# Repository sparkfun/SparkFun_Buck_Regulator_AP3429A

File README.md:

SparkFun AP3429A Buck Regulator Breakouts
========================================

<p align="center">

</p>

| [3.3V Buck Regulator (COM-21337)](https://www.sparkfun.com/products/21337) | [1.8V Buck Regulator (COM-21338)](https://www.sparkfun.com/products/21338) |
| --- | --- |
|  |  |

These buck regulator boards feature the AP3429A from [Diodes Inc.](https://www.diodes.com/), a 2A DC-DC buck converter with a wide input voltage range of 2.7V to 5.5V. The boards are configured to provide a regulated **3.3V** or **1.8V** output, which is controlled by an `EN` *(enable)* pin and indicated by a red power LED. A pre-assembled screw terminal and 0.1" spaced PTH pins are available to connect the input and output power of the boards. Additionally, there is the option to solder on a [barrel jack](https://www.sparkfun.com/products/119) for an [external power supply](https://www.sparkfun.com/categories/308). To dissipate excess heat, a copper pad is provided to attach a heat sink to the bottom of the board.

*The primary differences between these boards are their regulated output voltage (**1.8V** and **3.3V**) and the configured UVLO (**2.7V** and **3.9V**, respectively).*

Repository Contents
-------------------

* **[/docs](/docs/)** - Online documentation files
    * [board_files](/docs/board_files/) - Files for the product design
        * [Eagle design files](/docs/board_files/eagle_files.zip) (.zip)
        * [Schematic](/docs/board_files/schematic.pdf) (.pdf)
        * [Dimensions](/docs/board_files/dimensions.pdf) (.pdf)
    * [component_documentation](/docs/component_documentation/) - Datasheets for hardware components
    * [img/hookup_guide/](/docs/img/hookup_guide/) - Images for hookup guide documentation
* **[/Hardware](/Hardware/)** - Eagle design files (.brd, .sch)

Documentation
--------------
* **[Hookup Guide (mkdocs)](http://docs.sparkfun.com/SparkFun_Buck_Regulator_AP3429A/)** - Hookup Guide for the AP3429A Buck Regulator Breakouts

Product Variants
----------------
* **AP63357** - 5V Buck Regulators
    * COM-21255: [SparkFun Buck Regulator Breakout - 5V (AP63357DV)](https://www.sparkfun.com/products/21255)
    * COM-21256: [SparkFun BabyBuck Regulator Breakout - 5V (AP63357DV)](https://www.sparkfun.com/products/21256)
* **AP63203** - 3.3V Buck Regulators
    * COM-18356: [SparkFun Buck Regulator Breakout - 3.3V (AP63203)](https://www.sparkfun.com/products/18356)
    * COM-18357: [SparkFun BabyBuck Regulator Breakout - 3.3V (AP63203)](https://www.sparkfun.com/products/18357)
* **AP3429A** - 3.3V & 1.8V Buck Regulators
    * COM-21337: [SparkFun Buck Regulator Breakout - 3.3V (AP3429A)](https://www.sparkfun.com/products/21337)
    * COM-21338: [SparkFun Buck Regulator Breakout - 1.8V (AP3429A)](https://www.sparkfun.com/products/21338)

Version History
---------------
* [v01](https://github.com/sparkfun/SparkFun_Buck_Regulator_AP3429A/releases/tag/v01) - Initial Release

License Information
-------------------

This product is _**open source**_! 

Please review the LICENSE.md file for license information. 

If you have any questions or concerns about licensing, please contact technical support on our [SparkFun forums](https://forum.sparkfun.com/viewforum.php?f=152).

Distributed as-is; no warranty is given.

- Your friends at SparkFun.

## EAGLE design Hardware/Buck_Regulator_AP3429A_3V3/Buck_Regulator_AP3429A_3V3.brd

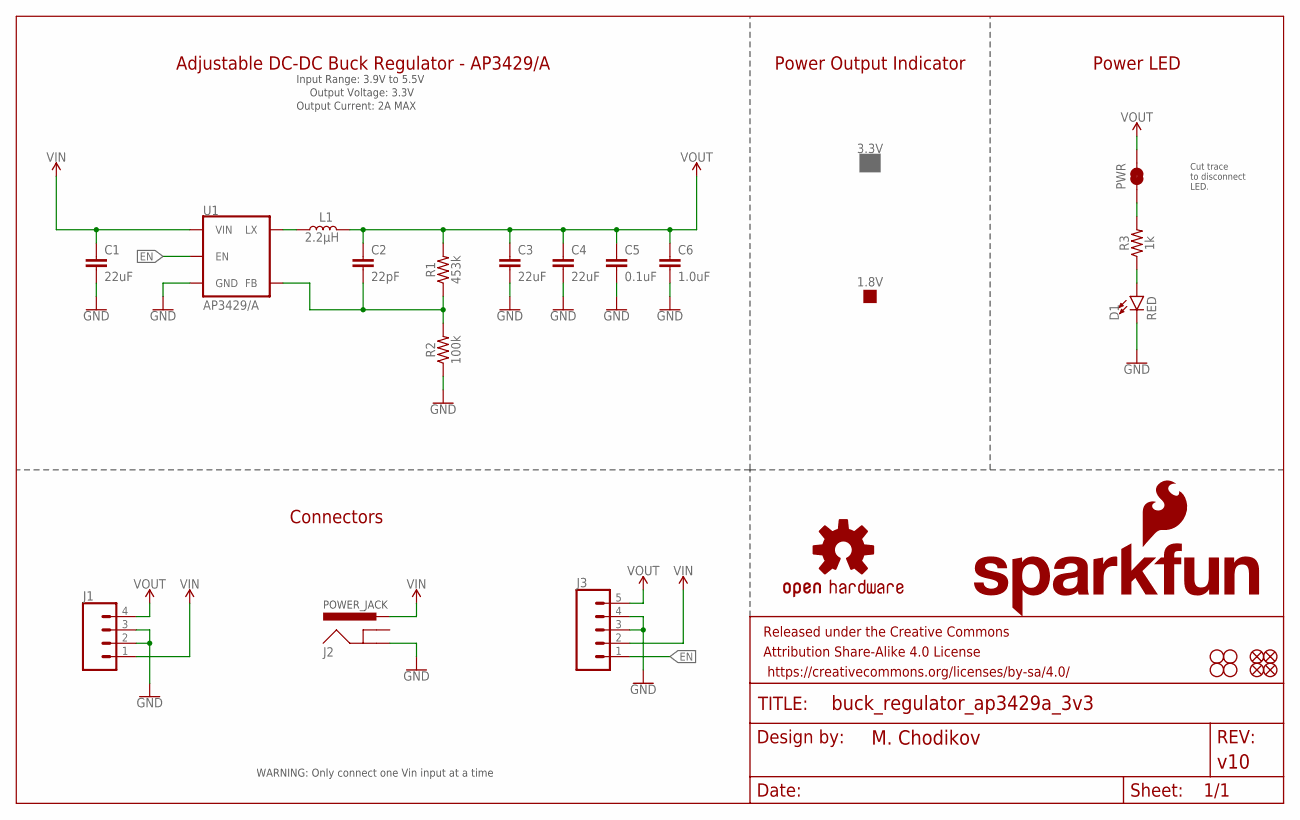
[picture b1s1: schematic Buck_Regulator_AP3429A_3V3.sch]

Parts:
1.8V: PROD_ID_NO-PASTE_NO_SILK; PRODUCT_IDENT_NO_NO-SILK
3.3V: PROD_ID_PASTE_NO-SILK; PRODUCT_IDENT_PASTE_NO-SILK
C1, C3, C4: 22uF; 0805
C2: 22pF; 0402-TIGHT
C5: 0.1uF; 0603
C6: 1.0uF; 0603
D1: RED; LED-0603
FD1, FD2, FD3, FD4: FIDUCIALUFIDUCIAL; FIDUCIAL-MICRO
FRAME1: FRAME-LEDGER; CREATIVE_COMMONS
H1, H2, H3, H4: STAND-OFFTIGHT; STAND-OFF-TIGHT
J1: Screw Terminal; SCREWTERMINAL-3.5MM-4
J2: POWER_JACKPOWER_JACK_SLOT_COMBO; POWER_JACK_PTH_SLOT_BOTH
J3: Breakout Headers; 1X05_NO_SILK
L1: 2.2μH; INDUCTOR_4X4MM
LOGO1: OSHW-LOGOS; OSHW-LOGO-S
LOGO2: SFE_LOGO_NAME.1_INCH; SFE_LOGO_NAME_.1
LOGO3: SFE_LOGO_FLAME.1_INCH; SFE_LOGO_FLAME_.1
PWR: JUMPER-SMT_2_NC_TRACE_SILK; SMT-JUMPER_2_NC_TRACE_SILK
R1: 453k; 0603
R2: 100k; 0603
R3: 1k; 0603
U1: AP3429/A; SOT23-5

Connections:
EN: J3.1, U1.1 (EN)
GND: C1.2, C3.2, C4.2, C5.2, C6.2, D1.C, J1.2, J1.3, J2.GND, J3.3, J3.4, R2.1, U1.2 (GND)
unnamed: L1.P$1 (1), U1.3 (LX)
unnamed: C2.2, R1.1, R2.2, U1.5 (FB)
unnamed: PWR.1, R3.2
unnamed: D1.A, R3.1
VIN: C1.1, J1.1, J2.PWR, J3.2, U1.4 (VIN)
VOUT: C2.1, C3.1, C4.1, C5.1, C6.1, J1.4, J3.5, L1.P$2 (2), PWR.2, R1.2

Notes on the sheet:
Input Range: 3.9V to 5.5V
Adjustable DC-DC Buck Regulator - AP3429/A
Power LED
Connectors
POWER_JACK
Output Current: 2A MAX
WARNING: Only connect one Vin input at a time
Power Output Indicator
Cut trace to disconnect LED.
Output Voltage: 3.3V

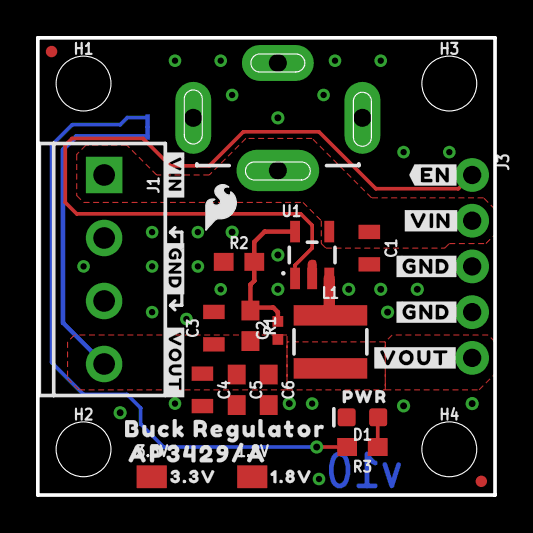
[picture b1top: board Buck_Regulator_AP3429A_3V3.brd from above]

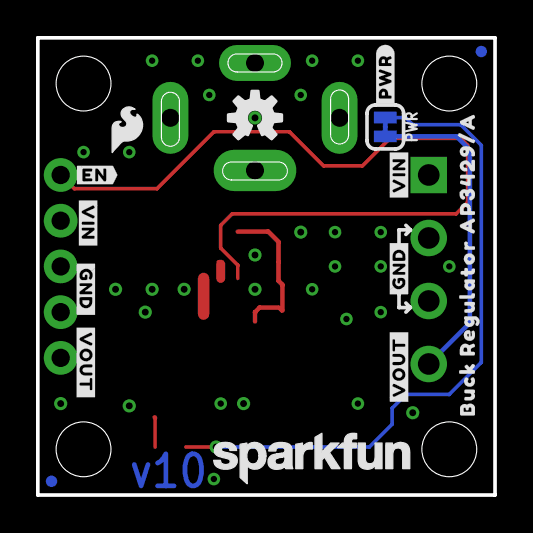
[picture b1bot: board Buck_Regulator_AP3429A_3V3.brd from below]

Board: 2 copper layers, 25.4 x 25.4 mm, 54 parts (15 on the bottom side), 8 nets.

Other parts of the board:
U$1: SFE_LOGO_FLAME_.1
U$2: BUCK_REGULATOR24
U$3: AP3429#A25
U$4: #VOUT#3431
U$5, U$6: #GND#3432
U$7: #VIN#3433
U$8, U$10: #GND#3446
U$9, U$15: #VIN#3445
U$11, U$13: #VOUT#3447
U$12: #EN#3448
U$14: #PWR#3451
U$16: BUCK_REGULATOR_AP3429#A3453
U$17: ORDERING_INSTRUCTIONS
U$19: 1#8V3441
U$20: PWR3441
U$21: #VOUT#3437
U$22: #VIN#3438
U$23: 3#3V3441
U$24: #GND#3439
U$25: #EN#3443

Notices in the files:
README.md:
License: MIT
parts and their libraries:
SparkFun-Jumpers: Licensing: Creative Commons ShareAlike 4.0 International - https://creativecommons.org/licenses/by-sa/4.0
SparkFun-Aesthetics: Released under the Creative Commons Attribution Share-Alike 4.0 License
SparkFun-Aesthetics: https://creativecommons.org/licenses/by-sa/4.0
